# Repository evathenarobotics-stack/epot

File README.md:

This is a starbie project by hacklife. A starbie is meant to be similar to a tamogatchi. Using KiCad's Schematic editor, I created circuits on the XIAO ESP32C3 inwhich the starbie can move via buttons and detect the enviornment with an enviornment sensor. This was then connected to the PCB and I chose a rounded heart shape as my base. In Arduino, I replicated the code given using my own wire managment and my starbie can draw hearts as well as little sparkles.

I turned it in late and lwk missed the dead line as a result of a mixture of errors and a busy schedule, however the errors I ran into were quite troublesome to manage. The code I replicated had errors running despite the lack of change at that point in the process.

But, I completed it and this is how the PCB board looks:

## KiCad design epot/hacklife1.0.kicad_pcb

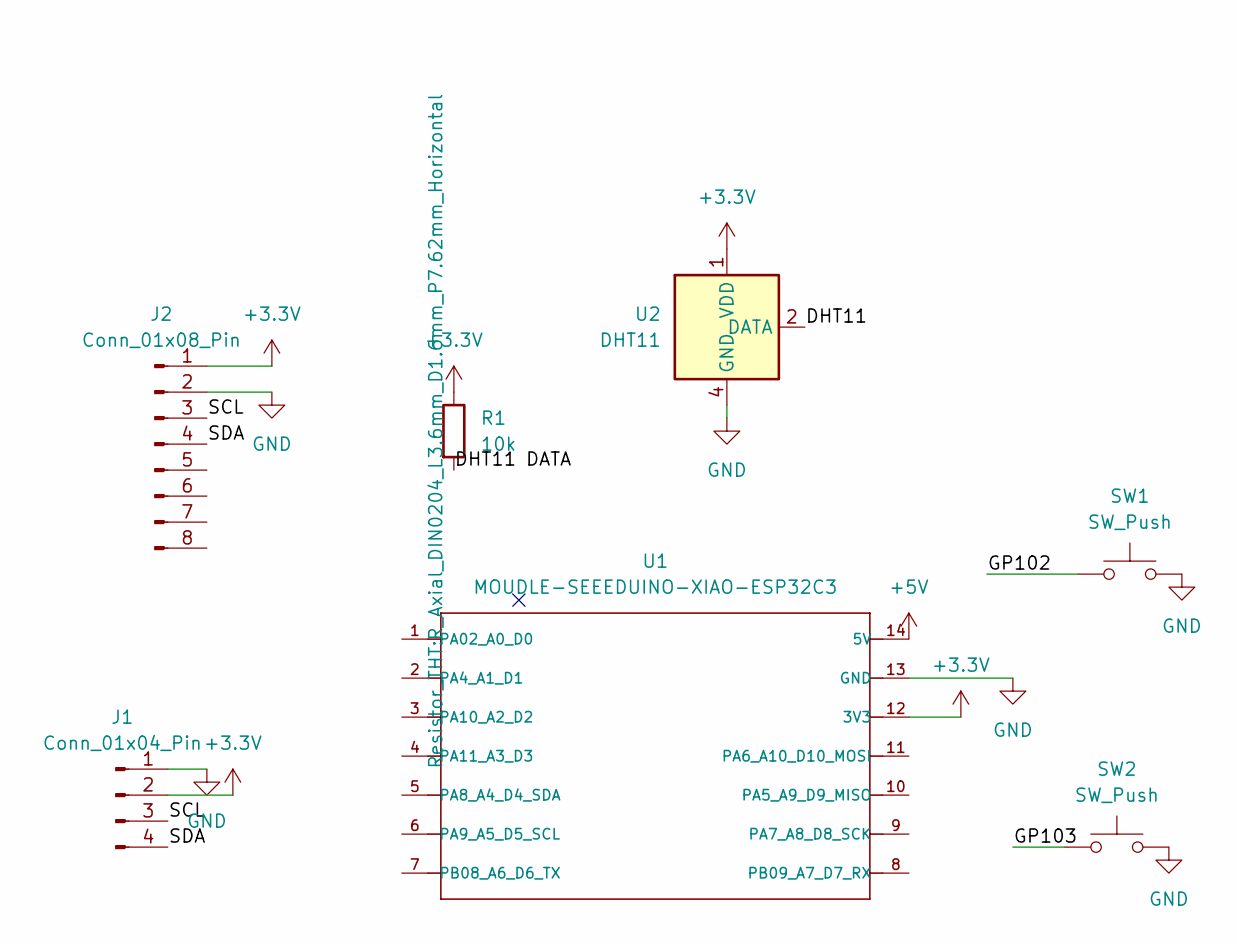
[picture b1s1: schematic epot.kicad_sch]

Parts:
J1: Conn_01x04_Pin; PinHeader_1x04_P2.54mm_Vertical
J2: Conn_01x08_Pin; PinHeader_1x08_P2.54mm_Vertical
R1: 10k; R_Axial_DIN0204_L3.6mm_D1.6mm_P7.62mm_Horizontal
SW1, SW2: SW_Push; SW_Cherry_MX_1.00u_PCB
U1: MOUDLE-SEEEDUINO-XIAO-ESP32C3; MCU_Seeed_ESP32C3
U2: DHT11; Aosong_DHT11_5.5x12.0_P2.54mm

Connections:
+3.3V: J1.2, J2.1, R1.1, U1.12 (3V3), U2.1 (VDD)
+5V: U1.14 (5V)
/DHT11: U2.2 (DATA)
/DHT11 DATA: R1.2
/GP102: SW1.1
/GP103: SW2.1
/SCL: J1.3, J2.3
/SDA: J1.4, J2.4
GND: J1.1, J2.2, SW1.2, SW2.2, U1.13 (GND), U2.4 (GND)

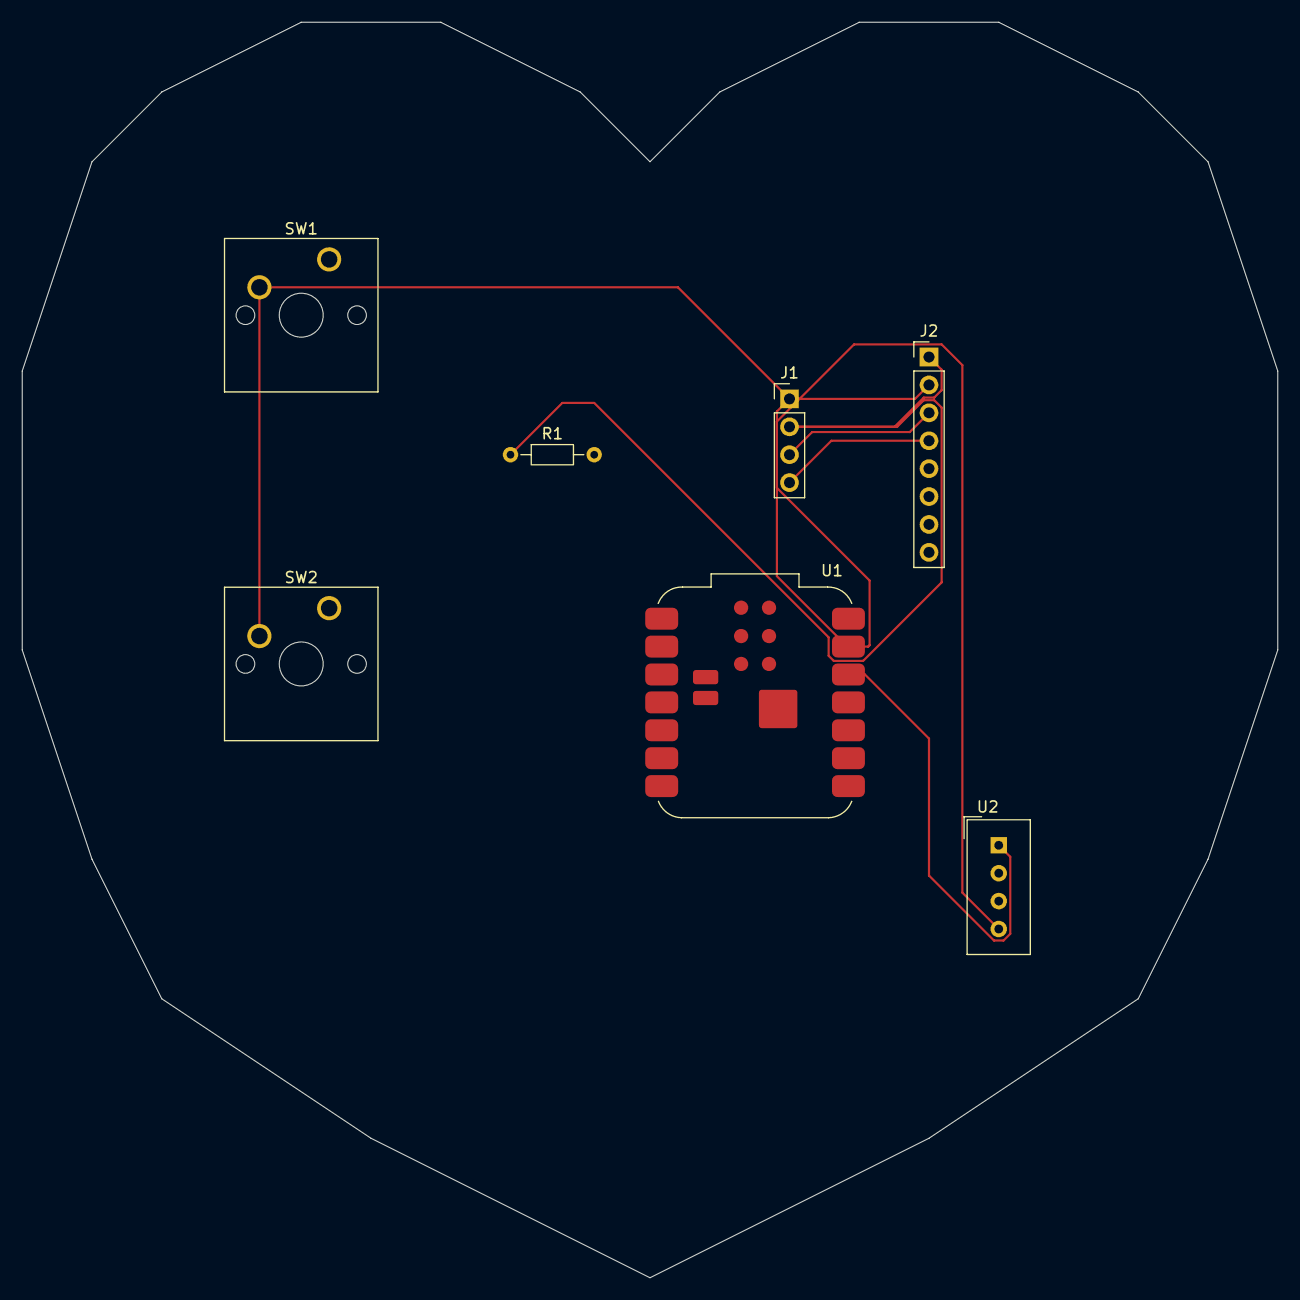
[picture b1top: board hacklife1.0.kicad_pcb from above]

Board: 2 copper layers, 114.3 x 114.3 mm, 7 parts (0 on the bottom side), 4 nets.
